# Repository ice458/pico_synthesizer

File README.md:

# Pico Synthesizer

A synthesizer project for the Raspberry Pi Pico 2.  

## Description

This project aims to create a functional 16-channel polyphonic synthesizer with a maximum of 20 voices running on the Raspberry Pi Pico 2 microcontroller. It includes various features like multiple waveform generation, envelope control, MIDI input processing, and more.

## Features

*   Polyphonic sound generation
*   Multiple waveforms (Sine, Sawtooth, Triangle, Square, Noise)
*   ADSR envelope
*   MIDI input processing (Note On/Off, Pitch Bend, CC messages)
*   PCM drum sample playback
*   Reverb effect (Master output)
*   Master volume and DC cut filter

## Tools

The `tools` directory contains Python scripts used to generate various data tables and C header files required by the synthesizer:

*   `wave_table.py`: Generates waveform tables and MIDI note-to-frequency increment tables.
*   `pitch_bend_table_interpolated.py`: Generates tables for pitch bend calculations.
*   `drum_table.py`: Processes a WAV file containing drum samples and converts them into C arrays for PCM playback.
*   `pan_table.py`: Generates tables for pan calculations.

## License

This project is licensed under the MIT License. See the `LICENSE` file for more details.

Additionally, the drum samples provided in `tools/drum/drum.wav` were generated using the `MuseScore_General.sf2` soundfont. The license for `MuseScore_General.sf2` can be found in `tools/drum/MuseScore_General_License.md`.

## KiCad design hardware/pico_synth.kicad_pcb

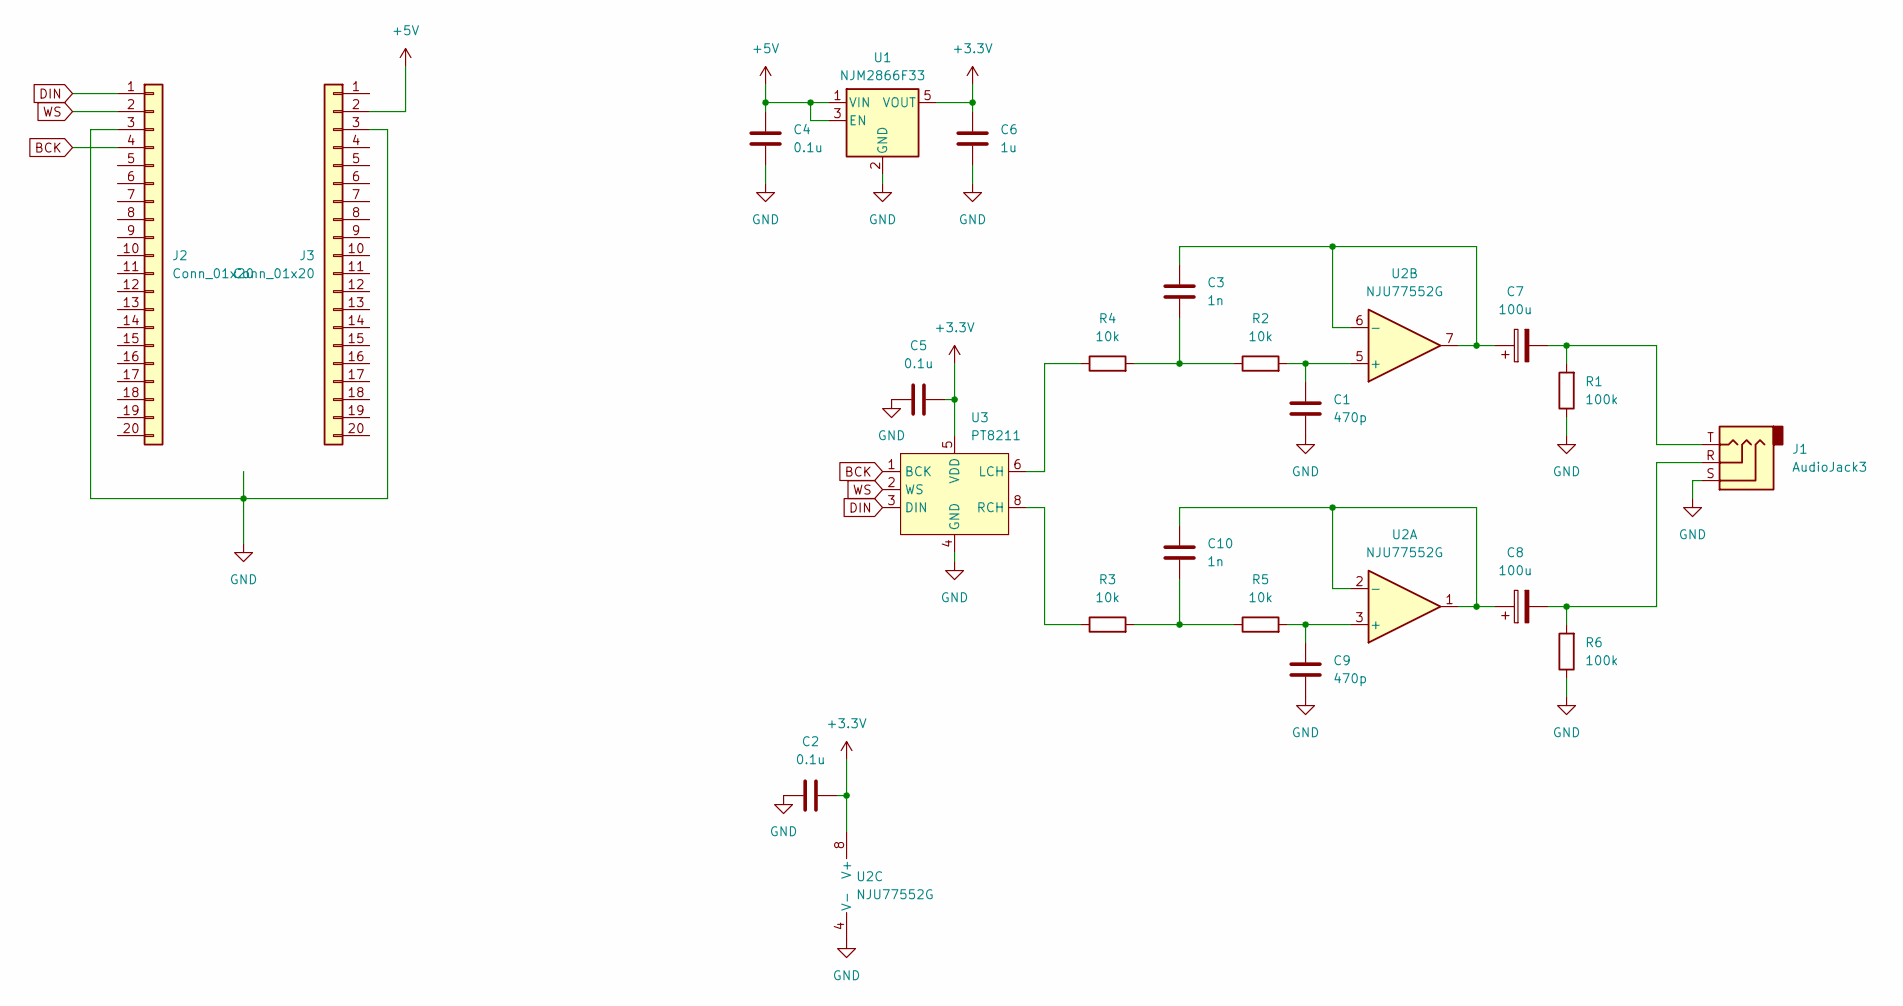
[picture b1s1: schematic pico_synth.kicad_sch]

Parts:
C1, C9: 470p; C_0603_1608Metric
C2, C4, C5: 0.1u; C_0603_1608Metric
C3, C10: 1n; C_0603_1608Metric
C6: 1u; C_0603_1608Metric
C7, C8: 100u; CP_Radial_D6.3mm_P2.50mm
J1: AudioJack3; Jack_3.5mm_Switronic_ST-005-G_horizontal
J2, J3: Conn_01x20; PinHeader_1x20_P2.54mm_Vertical
R1, R6: 100k; R_0603_1608Metric
R2, R3, R4, R5: 10k; R_0603_1608Metric
U1: NJM2866F33; SOT-23-5
U2: NJU77552G; SO-8_3.9x4.9mm_P1.27mm
U3: PT8211; SO-8_3.9x4.9mm_P1.27mm

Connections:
+3.3V: C2.2, C5.2, C6.1, U1.5 (VOUT), U2.8 (V+), U3.5 (VDD)
+5V: C4.1, J3.2, U1.1 (VIN), U1.3 (EN)
BCK: J2.4, U3.1 (BCK)
DIN: J2.1, U3.3 (DIN)
GND: C1.2, C2.1, C4.2, C5.1, C6.2, C9.2, J1.S, J2.3, J3.3, R1.1, R6.1, U1.2 (GND), U2.4 (V-), U3.4 (GND)
unnamed: C3.2, R2.1, R4.2
unnamed: C7.2, J1.T, R1.2
unnamed: C8.2, J1.R, R6.2
unnamed: C10.2, R3.2, R5.1
unnamed: C9.1, R5.2, U2.3 (+)
unnamed: C8.1, C10.1, U2.1, U2.2 (-)
unnamed: C1.1, R2.2, U2.5 (+)
unnamed: C3.1, C7.1, U2.6 (-), U2.7
unnamed: R4.1, U3.6 (LCH)
unnamed: R3.1, U3.8 (RCH)
WS: J2.2, U3.2 (WS)

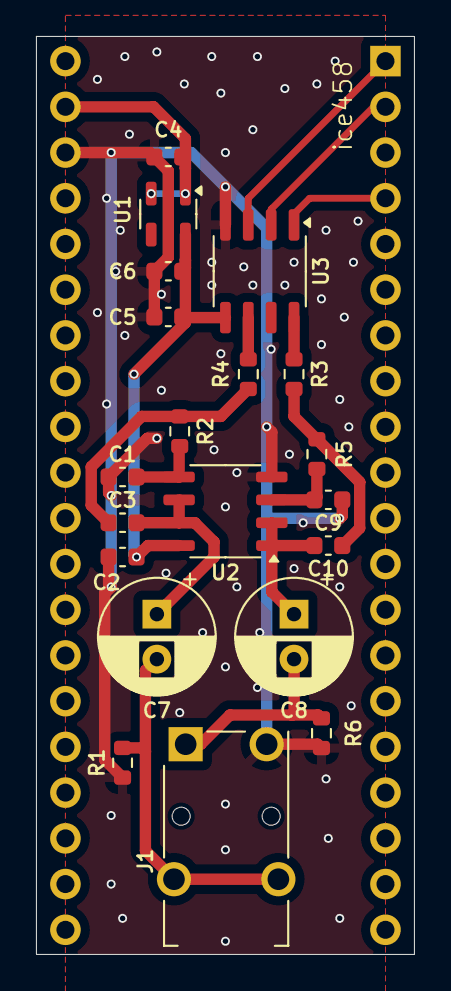
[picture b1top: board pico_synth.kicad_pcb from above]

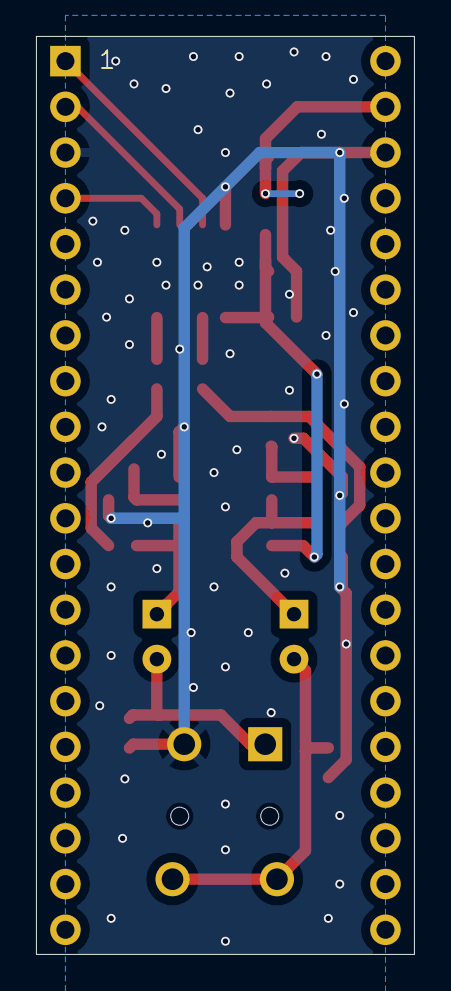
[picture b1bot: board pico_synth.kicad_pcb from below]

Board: 2 copper layers, 21.0 x 51.0 mm, 22 parts (2 on the bottom side), 16 nets.

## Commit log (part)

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2025-06-11 gitignore
2025-06-11 image
2025-06-11 change
2025-06-22 ノイズ対策でボイスのLPFをコメントアウト
2025-06-22 PBバク修正
2025-06-22 RPN NRPNでMSBのみを受信した場合にも値を処理するように修正
2025-06-28 ADPCM対応
